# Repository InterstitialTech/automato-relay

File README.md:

# automato-relay
relay module for the Automato ecosystem

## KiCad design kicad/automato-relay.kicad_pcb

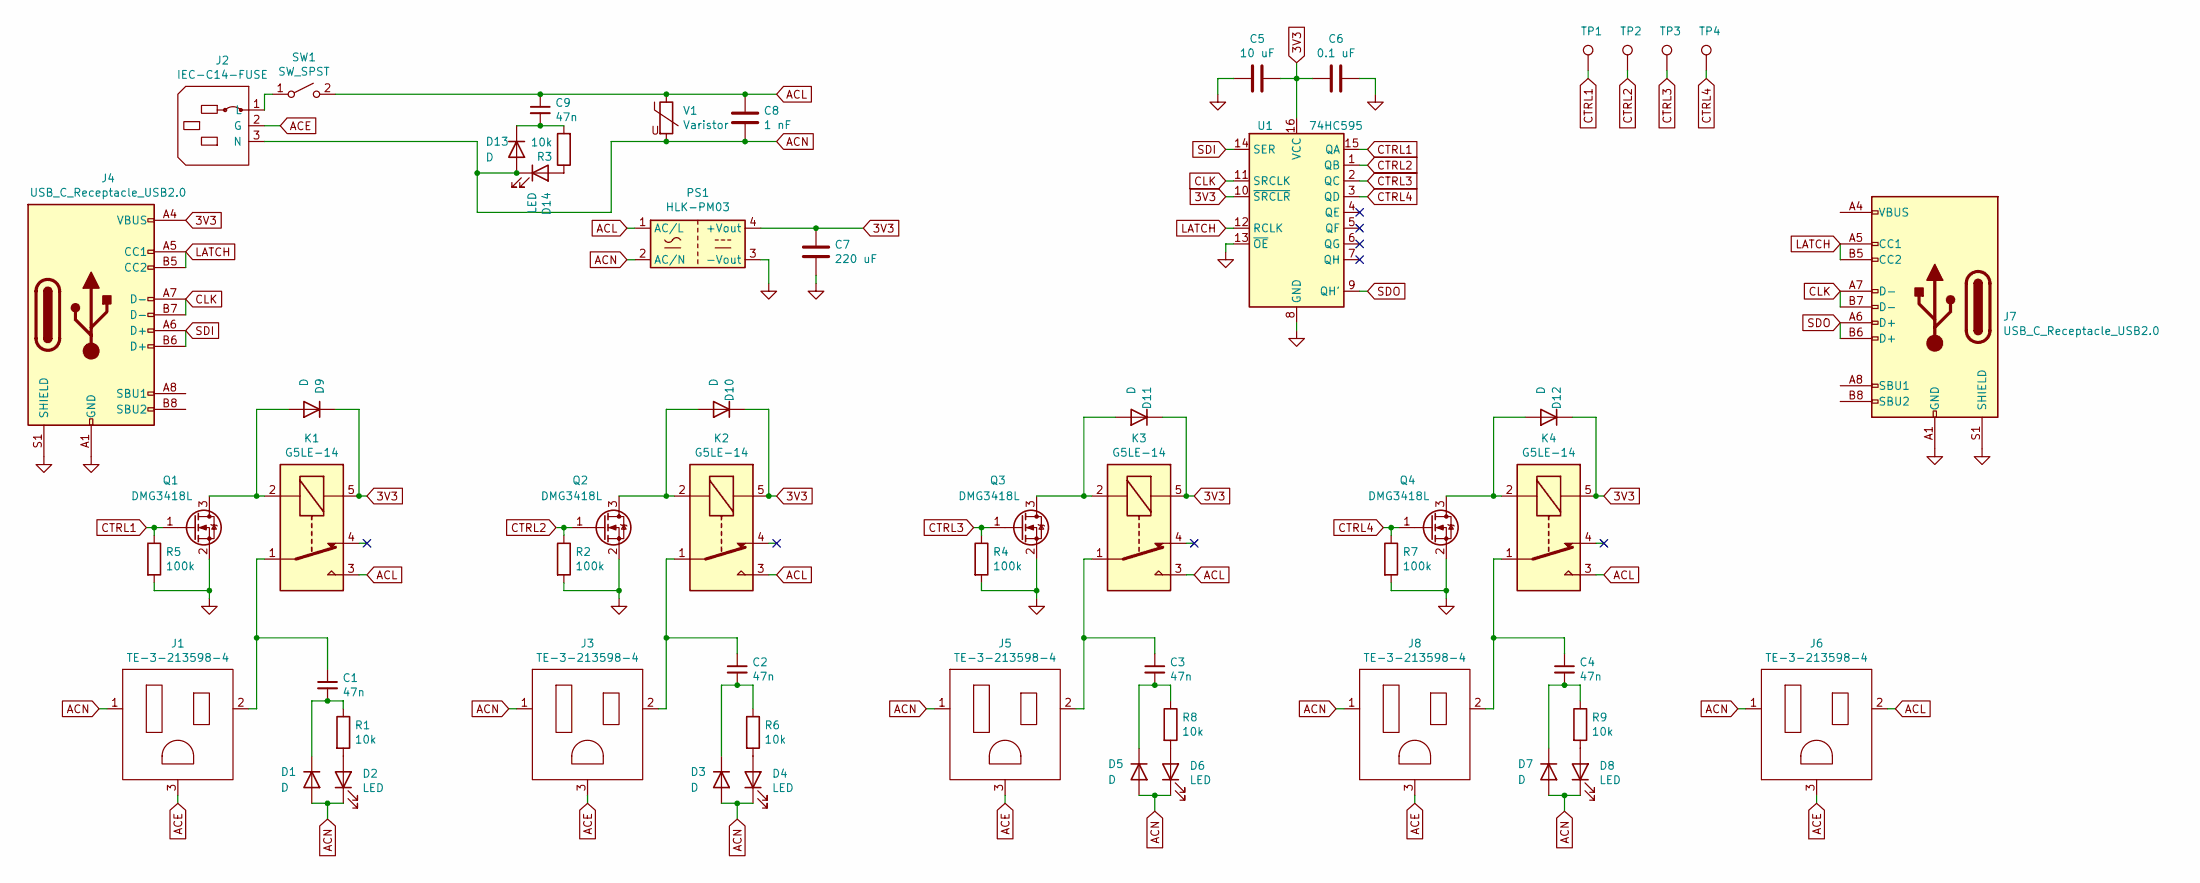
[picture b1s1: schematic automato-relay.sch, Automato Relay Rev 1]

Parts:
C1, C2, C3, C4, C9: 47n; C_1206_3216Metric
C5: 10 uF; C_1206_3216Metric
C6: 0.1 uF; C_1206_3216Metric
C7: 220 uF; CP_Radial_D6.3mm_P2.50mm
C8: 1 nF; C_Disc_D7.5mm_W5.0mm_P10.00mm
D1, D3, D5, D7, D13: D; D_SOD-123
D2, D4, D6, D8, D14: LED; LED_1206_3216Metric
D9, D10, D11, D12: D; D_SOT-23_ANK
J1, J3, J5, J6, J8: TE-3-213598-4
J2: IEC-C14-FUSE; PF0011-15-PC
J4, J7: USB_C_Receptacle_USB2.0; USB_C_Receptacle_GCT-USB4105
K1, K2, K3, K4: G5LE-14; Relay_SPDT_Omron-G5LE-1
PS1: HLK-PM03; Converter_ACDC_HiLink_HLK-PMxx
Q1, Q2, Q3, Q4: DMG3418L; SOT-23
R1, R3, R6, R8, R9: 10k; R_0805_2012Metric
R2, R4, R5, R7: 100k; R_0805_2012Metric
SW1: SW_SPST; RA1H1C112R
TP1, TP2, TP3, TP4: TestPoint; PinHeader_1x01_P2.54mm_Vertical
U1: 74HC595; SO-16_3.9x9.9mm_P1.27mm
V1: Varistor; RV_Disc_D15.5mm_W3.9mm_P7.5mm

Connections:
3V3: C5.1, C6.2, C7.1, D9.1 (K), D10.1 (K), D11.1 (K), D12.1 (K), J4.A4 (VBUS), J4.A9 (VBUS), J4.B4 (VBUS), J4.B9 (VBUS), K1.5, K2.5, K3.5, K4.5, PS1.4 (+Vout), U1.10 (~SRCLR), U1.16 (VCC)
ACE: J1.3 (Earth), J2.2 (G), J3.3 (Earth), J5.3 (Earth), J6.3 (Earth), J8.3 (Earth)
ACL: C8.1, C9.1, J6.2 (Hot), K1.3, K2.3, K3.3, K4.3, PS1.1 (AC/L), SW1.2 (B), V1.1
ACN: C8.2, D1.2 (A), D2.1 (K), D3.2 (A), D4.1 (K), D5.2 (A), D6.1 (K), D7.2 (A), D8.1 (K), D13.2 (A), D14.1 (K), J1.1 (Neutral), J2.3 (N), J3.1 (Neutral), J5.1 (Neutral), J6.1 (Neutral), J8.1 (Neutral), PS1.2 (AC/N), V1.2
CLK: J4.A7 (D-), J4.B7 (D-), J7.A7 (D-), J7.B7 (D-), U1.11 (SRCLK)
CTRL1: Q1.1 (G), R5.1, TP1.1, U1.15 (QA)
CTRL2: Q2.1 (G), R2.1, TP2.1, U1.1 (QB)
CTRL3: Q3.1 (G), R4.1, TP3.1, U1.2 (QC)
CTRL4: Q4.1 (G), R7.1, TP4.1, U1.3 (QD)
GND: C5.2, C6.1, C7.2, J4.A1 (GND), J4.A12 (GND), J4.B1 (GND), J4.B12 (GND), J4.S1 (SHIELD), J7.A1 (GND), J7.A12 (GND), J7.B1 (GND), J7.B12 (GND), J7.S1 (SHIELD), PS1.3 (-Vout), Q1.2 (S), Q2.2 (S), Q3.2 (S), Q4.2 (S), R2.2, R4.2, R5.2, R7.2, U1.8 (GND), U1.13 (~OE)
LATCH: J4.A5 (CC1), J4.B5 (CC2), J7.A5 (CC1), J7.B5 (CC2), U1.12 (RCLK)
unnamed: C1.1, J1.2 (Hot), K1.1
unnamed: C1.2, D1.1 (K), R1.1
unnamed: C2.1, J3.2 (Hot), K2.1
unnamed: C2.2, D3.1 (K), R6.1
unnamed: C3.1, J5.2 (Hot), K3.1
unnamed: C3.2, D5.1 (K), R8.1
unnamed: C4.1, J8.2 (Hot), K4.1
unnamed: C4.2, D7.1 (K), R9.1
unnamed: C9.2, D13.1 (K), R3.2
unnamed: D2.2 (A), R1.2
unnamed: D4.2 (A), R6.2
unnamed: D6.2 (A), R8.2
unnamed: D8.2 (A), R9.2
unnamed: D9.2 (A), K1.2, Q1.3 (D)
unnamed: D10.2 (A), K2.2, Q2.3 (D)
unnamed: D11.2 (A), K3.2, Q3.3 (D)
unnamed: D12.2 (A), K4.2, Q4.3 (D)
unnamed: D14.2 (A), R3.1
unnamed: J2.1 (L), SW1.1 (A)
unnamed: J7.A4 (VBUS), J7.A9 (VBUS), J7.B4 (VBUS), J7.B9 (VBUS)
SDI: J4.A6 (D+), J4.B6 (D+), U1.14 (SER)
SDO: J7.A6 (D+), J7.B6 (D+), U1.9 (QH')

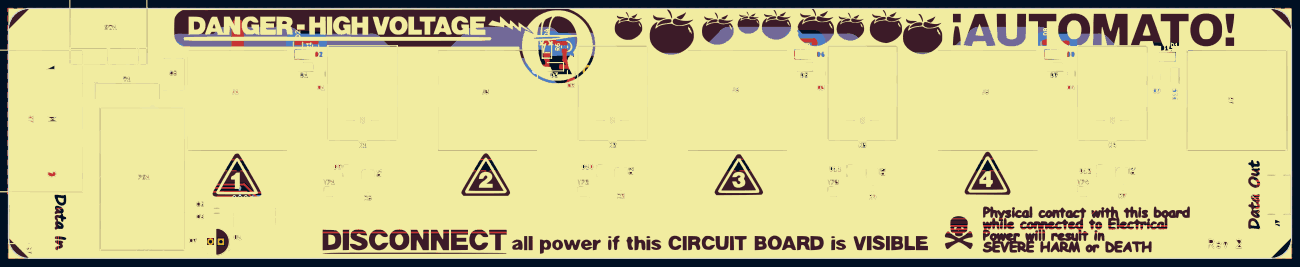
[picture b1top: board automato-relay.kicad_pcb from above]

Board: 2 copper layers, 308.0 x 60.0 mm, 56 parts (0 on the bottom side), 33 nets.

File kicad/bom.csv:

Reference,Quantity,Value,Manufacturer,Manufacturer Part Number,Digikey Part Number
"D1, D3, D5, D7, D9, D10, D11, D12",4,D,ON Semiconductor,BAS16LT1G,BAS16LT1GOSCT-ND
"D2, D4, D6, D8",4,LED,Würth Elektronik,150120GS75000,732-4990-1-ND
"J1, J3, J5, J6, J8",5,TE-3-213598-4,TE Connectivity AMP Connectors,3-213598-4,3-213598-4-ND
J2,1,Screw_Terminal_01x03,Phoenix Contact,1935789,277-6072-ND
"J4, J7",1,Screw_Terminal_01x05,Phoenix Contact,1935190,277-1580-ND
"K1, K2, K3, K4",4,G5LE-14,Omron Electronics Inc-EMC Div,G5LE-14 DC3,Z3326-ND
PS1,1,HLK-PM03,Hi-Link,HLK-PM03,
"Q1, Q2, Q3, Q4",4,DMG3418L,Diodes Incorporated,DMG3418L-7,DMG3418L-7DICT-ND
"C1, C2, C3, C4",4,0.047uF,Kemet,C1206C473KAREC7800,399-C1206C473KAREC7800CT-ND
"R1, R2, R3, R4",4,100k,Yageo,RC0805FR-07100KL,311-100KCRCT-ND
U1,1,74HC595,Toshiba Semiconductor and Storage,74HC595D,74HC595DCT-ND
V1,1,TMOV14RP140E ,"Littlefuse, Inc",TMOV14RP140E ,F4004-ND

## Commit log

2021-02-03 fix copy-paste error: CTRL1/2/3/4
2021-02-05 annotate symbols
2021-02-08 remove SPDT switches
2021-02-08 ground LEDs through ACN
2021-02-08 add low-side mosfets for relay coils
2021-02-08 add earth ground connections
2021-02-08 add pull-down resistors to MOSFET gates
2021-02-09 add TE-3-213598-4 symbol
2021-02-09 add TE-3-213598-4 footprint
2021-02-09 increase schematic width
2021-02-09 remove 3V3 from J7
2021-02-11 add bom.csv
2021-02-11 add schematic_20210209.png
2021-02-11 README.md: add schematic image
2021-02-23 All traces routed
    MOV added, 10 hours in. Final approval of layout. Power planes to pour.
2021-02-25 Final Rev
    Added varistor, poured power planes, added mounting holes, modified data headers, added space for IEC connector.
2021-02-25 resized capacitors
    forgot to resize capacitors in schematic
2021-02-25 layout: remove vias on SDO
2021-02-25 layout: add Earth pour on southern half of board (both sides)
2021-02-25 layout: add GND and 3V3 pours on northern half of board
2021-02-25 layout: modify and move revision label
2021-02-25 layout: replace mounting holes with proper M3 pads, add rounded corners
2021-02-25 add testpoints for CTRL1,2,3,4
2021-02-25 move bom.csv to top level
2021-02-25 schematic: add metadata
2021-02-25 update schematic, layout, and render for Rev 1
2021-02-25 README: update assets
2021-03-06 bom.csv: correct quanitity on BAS16LT1G diodes
2021-03-08 add PhoenixContact_1935190_1x5.kicad_mod
2021-03-10 update J4/J7 footprints to Phoenix 1935190
2021-03-10 layout: add silkscreen pin labels for J4 and J7
2021-07-09 add decoupling capacitors for the 74HC595
2021-07-09 add decoupling capacitor for the HLK-PM03
2021-07-09 add X1 safety capacitor across AC lines
2021-07-16 layout: increase priority level on rear ACL zone
2021-07-16 layout: minor changes to appease DRC
2021-07-16 update assets as of 20210715
2021-09-14 bom.csv: fix old reference designators R1, R3
2022-02-15 Changed Indicator bypass diodes to 1000V reverse-voltage diodes (1n4007)
2022-02-15 Changed indicator diode footprint and re-routed
2022-02-15 updated BOM to reflect indicator bypass diode change
2022-03-06 added IEC-C14 to library
2022-03-06 added fused inlet
2022-03-06 swapped iec inlet pins to match footprint
2022-03-06 removed screw terminals, add IEC inlet + switch
2022-03-06 Starting to play with pcb layout for new rev.
    Moved outlets to top of board to make power switch placement more sensical.
2022-03-06 updating the caches and .pro file
2022-03-06 routed high power section
2022-03-07 playing around with 5-pin connector location
2022-03-10 added usb-c receptacle to library
2022-03-10 replaced 5-pin connectors with usb-c receptacles
2022-03-10 add usb-c receptacle
2022-03-10 add usb-c receptacles, begin digital routing
2022-03-10 finished routing logic
2022-03-10 mostly finished power routing
2022-03-10 routing for v2 looking good. waiting for review
2022-03-10 replaced screw terminals with usb-C
2022-03-11 shifted usb-C connector location
2022-03-12 add silk screen footprint
2022-03-12 finalizing v2 silk screen. GERB EXPORT
2022-03-13 update usb-C receptacle footprint
    for yellow soldermask, minimum thickness is 0.22mm
2022-03-13 update usb-C receptacles
2022-03-27 added resistors to led indicators
2022-03-27 added resistors and thermal spacing on pours
2022-03-27 added eu-outlet
2022-03-27 add automato-relay-eu
2022-03-27 update silk
2022-03-27 Update fp-info-cache
2022-04-04 change usb c -> spi pinout
2022-04-04 update gitignore
